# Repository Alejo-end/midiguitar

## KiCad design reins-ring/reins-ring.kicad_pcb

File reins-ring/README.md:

# REINS LED ring (replaces the Adafruit NeoPixel Ring 16)

This is a 2 layer JLCPCB board with 16 WS2812B LEDs (5050) on the top and one 100 nF 0603 cap per LED (LCSC C14663) on the back. JLCPCB solders the 16 LEDs. You solder the 16 caps and three wires to round pads on the flat back face. Nothing hides these pads.

The board file names the LED as LCSC C114586. JLCPCB no longer offers that part, so `export_jlc.py` writes C52917433 (Worldsemi WS2812B-V6, same SMD5050-4P package) into the order files (`SUBST`). Check the pin order in its data sheet before you approve: 1 VDD, 2 DOUT, 3 VSS, 4 DIN.

## Numbers [M]

| Item | Value |
| --- | --- |
| Outline | a plain ring, outer diameter 44.4 mm, bore 31.75 mm (same bore as the Adafruit ring) |
| Board thickness | 0.8 mm. Choose this in the JLCPCB cart. The LED stands about 1.6 mm above the board [D], so board plus LED is 2.4 mm |
| LEDs | 16, center radius 18.9 mm, every 22.5 degrees |
| Caps | on the back, 0603, 0.55 mm high at most [R]. They sit at radius 17.6 to 20.2 mm |
| Wire pads | 3 round SMD pads of 1.5 mm on the back, in a radial row at radius 17.2 (GND), 19.0 (DIN) and 20.8 mm (5V) |

## Wire pads

1. The row sits in the gap between LED16 and LED1. The gap is 2.4 mm wide between the LED bodies. The pads need 1.5 mm. The nearest copper of another net is the notch of the band at 0.2 mm, and the nearest via is 2.5 mm away [M].
2. `PAD_ANGLE` in `make_ring.py` sets where the row sits, as seen from the top. The default is 0, which is +X on the sheet, counter clockwise. The pod turns the ring on its seat, so any angle works. Set it, run the script and export again.
3. The back silk shows one letter beside each pad: G for GND, D for DIN and 5 for 5V. The back view is mirrored.
4. The pads are plain copper. They carry no part and no paste. The 5V and GND pads touch their copper band through spokes, so the iron can heat them.
5. The pad copper reaches radius 16.45 to 21.55 mm. In the pod, the wire slot (radius 16.6 to 22.2 mm) is open under the pads, so no rim touches the solder joints. Turn the ring until the pad gap lines up with the slot.

## Pod interface (back side)

1. Everything on the back that has height is a cap, at most 0.8 mm tall. The caps and the wire joints must fit in the groove of the pod, which is 1.2 mm deep and spans radius 17.4 to 22.4 mm (open at the outer edge). The ring rests on the inner rim and on three outer posts at 90, 210 and 330 degrees in the pod frame.
2. Nothing on the back with height reaches beyond that radius range. The back copper bands are flat and span radius 16.2 to 22.2 mm.
3. The ring turns on its seat to match the pod slot.

## Circuit

1. 5V and GND come in at the pads. The ring has no regulator and no level shifter. The guitar board keeps the level shifter and the 330 ohm resistor.
2. DIN goes through a via beside its pad to LED1. Each LED passes the data to the next one counter clockwise. DOUT of LED16 stays open.
3. The back has two bands: the outer band is 5V and the inner band is GND. Each cap sits across the two bands under its LED. Vias join the LED pads to the bands.
4. For a current budget: 16 LEDs at full white take about 960 mA [R]. The guitar firmware keeps the brightness low by default.

## Files

| File | What it is |
| --- | --- |
| `make_ring.py` | Writes `reins-ring.kicad_pcb` and `reins-ring.kicad_pro`. There is no schematic: this script holds the netlist |
| `drc.sh` | Runs the KiCad DRC on a temp copy with refilled zones |
| `export_jlc.py` | Writes `fab/jlc/reins-ring/` with the Gerber zip, the BOM and the CPL for both sides, and `-top` BOM and CPL files with the 16 LEDs only |
| `renders/` | Top and bottom pictures |

Run the two scripts with the KiCad Python (`/Applications/KiCad/KiCad.app/Contents/Frameworks/Python.framework/Versions/3.9/bin/python3`).

## Order notes

1. Choose Economic PCB Assembly, top side, and upload `reins-ring-top-bom.csv` and `reins-ring-top-cpl.csv`. Economic assembly places one side only, and Standard assembly needs a board of at least 70 x 70 mm. Solder the 16 caps (100 nF 0603) on the back by hand, across the two copper bands. The wire pads are plain copper and need no part.
2. Choose 0.8 mm thickness. The Gerber files do not carry the thickness.
3. Make sure that the pin 1 of each LED matches the placement picture from JLCPCB. Pin 1 (VDD) is the pad on the outer edge, on the counter clockwise side. The DIN pad is on the outer edge, on the clockwise side. Do not approve if one LED differs. The rotation that JLCPCB expects for C52917433 is not confirmed, so `ROT` in `export_jlc.py` is 0 [E]. If every LED is turned the same wrong way, set the correction there and export again.
4. The caps are symmetric parts, so a 180 degree error does not matter.

## DRC [M]

The KiCad DRC on the refilled board shows 0 violations and no unconnected items, with the JLCPCB 2 layer limits (0.15 mm track and clearance, 0.3 mm copper to edge). The courtyard check is off, because the LED courtyards touch in the ring. I did not simulate the board and I did not build one.

## Cost (estimate, not a quote)

I did not get a JLCPCB quote. The LED is about 6 cents each in a cached LCSC listing [R], so 16 LEDs are about 1 euro. The rest is the board, the one time assembly setup fee and shipping. If the LED or C14663 is an Extended part, JLCPCB adds a fee per part type. Put the board in the cart to see the real price. A ring ordered alone is probably not cheaper than the Adafruit ring for one unit. It becomes cheaper in a batch, or when you add it to another JLCPCB order that you already pay for.

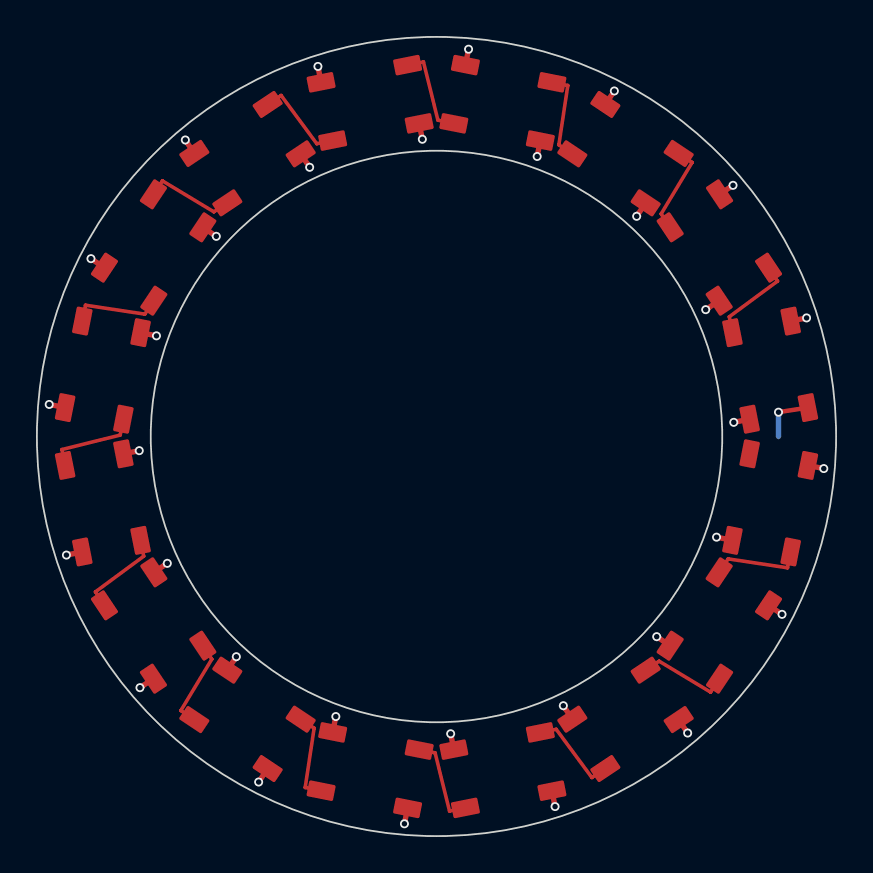
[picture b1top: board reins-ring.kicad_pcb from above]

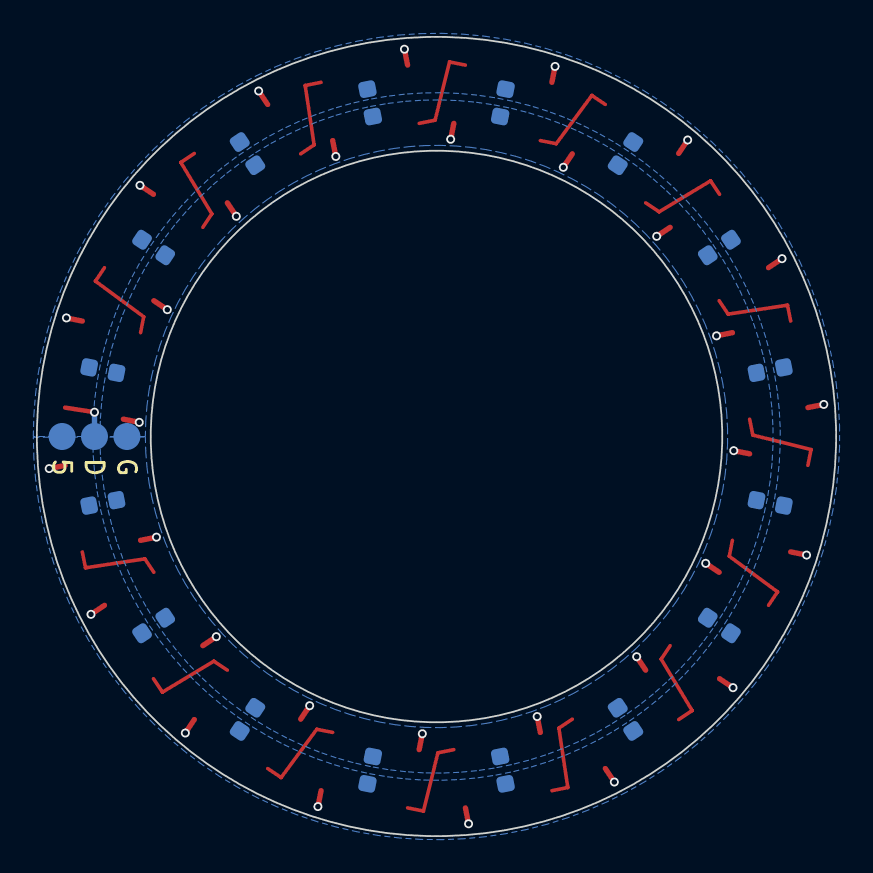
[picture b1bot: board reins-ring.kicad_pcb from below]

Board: 2 copper layers, 44.4 x 44.4 mm, 35 parts (16 on the bottom side), 18 nets.

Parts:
C1, C2, C3, C4, C5, C6, C7, C8, C9, C10, C11, C12, C13, C14, C15, C16: 100nF; C_0603_1608Metric
LED1, LED2, LED3, LED4, LED5, LED6, LED7, LED8, LED9, LED10, LED11, LED12, LED13, LED14, LED15, LED16: WS2812B; LED_WS2812B_PLCC4_5.0x5.0mm_P3.2mm
W_5V: 5V
W_DIN: DIN
W_GND: GND

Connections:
5V: C1.2, C2.2, C3.2, C4.2, C5.2, C6.2, C7.2, C8.2, C9.2, C10.2, C11.2, C12.2, C13.2, C14.2, C15.2, C16.2, LED1.1, LED2.1, LED3.1, LED4.1, LED5.1, LED6.1, LED7.1, LED8.1, LED9.1, LED10.1, LED11.1, LED12.1, LED13.1, LED14.1, LED15.1, LED16.1, W_5V.1
D1: LED1.2, LED2.4
D2: LED2.2, LED3.4
D3: LED3.2, LED4.4
D4: LED4.2, LED5.4
D5: LED5.2, LED6.4
D6: LED6.2, LED7.4
D7: LED7.2, LED8.4
D8: LED8.2, LED9.4
D9: LED9.2, LED10.4
D10: LED10.2, LED11.4
D11: LED11.2, LED12.4
D12: LED12.2, LED13.4
D13: LED13.2, LED14.4
D14: LED14.2, LED15.4
D15: LED15.2, LED16.4
DIN: LED1.4, W_DIN.1
GND: C1.1, C2.1, C3.1, C4.1, C5.1, C6.1, C7.1, C8.1, C9.1, C10.1, C11.1, C12.1, C13.1, C14.1, C15.1, C16.1, LED1.3, LED2.3, LED3.3, LED4.3, LED5.3, LED6.3, LED7.3, LED8.3, LED9.3, LED10.3, LED11.3, LED12.3, LED13.3, LED14.3, LED15.3, LED16.3, W_GND.1

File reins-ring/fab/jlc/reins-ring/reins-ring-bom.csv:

Comment,Designator,Footprint,LCSC
100nF,"C1,C2,C3,C4,C5,C6,C7,C8,C9,C10,C11,C12,C13,C14,C15,C16",C_0603_1608Metric,C14663
WS2812B,"LED1,LED2,LED3,LED4,LED5,LED6,LED7,LED8,LED9,LED10,LED11,LED12,LED13,LED14,LED15,LED16",LED_WS2812B_PLCC4_5.0x5.0mm_P3.2mm,C114586
